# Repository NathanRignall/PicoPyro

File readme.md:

# Pico Pyro v1.0.1
DMX controlled dual pyrotechnic channels.

## Hardware Overview

 - Status LED - (WHITE, GREEN, RED, BLUE, PURPLE)
 - Continuity LED - (GREEN)
 - Fire LED - (RED)
 - Configuration Button
 - Arming Cover
 - DMX In/Out

 - Power+ (3v-50v)
 - Power-
 - Pyro 0/1-
 - Pyro 0/1+

## Modes
The Pico Pyro can be in one of three modes, these are indicated by the status LED.

By default the system enters **active** mode when turned on.

To enter **setup** mode the configuration button must be pressed while being turned on. Setup mode cannot be entered after booting.

If the system detects an invalid configuration during boot the system will enter **failed** mode. To resolved the system must be turned off and back on into setup mode.

### Active
 - Status LED is solid **GREEN** when DMX is detected, **RED** when no DMX signal is detected.
 - Continuity LEDs are **GREEN** when the voltage threshold is met across the pyrotechnic channels. These are used to show if there is a good connection across the hardware connected.
 - Fire LEDs are **RED** when the specified pyrotechnic channel is fired. This occurs when the DMX authorization and fire values are met for that channel.

### Setup
 - Status LED **BLUE**.
 - Continuity LEDs are **GREEN** when the voltage threshold is met across the pyrotechnic channels. These are used to show if there is a good connection across the hardware connected.
 - Fire LEDs and hence pyrotechnic channels off and ***cannot activate***.

### Failed
 - Status LED **PURPLE**.
 - Continuity LEDs off and cannot activate.
 - Fire LEDs and hence pyrotechnic channels off and ***cannot activate***.

## DMX Table

| Channel | Description                         |
| ------- | ----------------------------------- |
| 1       | Pyrotechnic Channel 0 Authorization |
| 2       | Pyrotechnic Channel 1 Authorization |
| 3       | Pyrotechnic Channel 0 Fire          |
| 4       | Pyrotechnic Channel 1 Fire          |

The DMX values to activate the different channels are specified in the configuration tool.

## Setup
Once entering setup mode the system can be configured using the built-in website. This is accessed by connecting to the WiFi network that is broadcast and navigating to the IP address in the chosen browser.

**SSID** - PicoPyro  
**Password** - itsathing  
**URL** - http://10.66.0.1

The user should be presented with the following...

 - Voltage threshold - (0-1023) - Value used to activate the continuity LEDs. This value is dependant on the supplied voltage. When supplied with around 12v an advised threshold value is 100.
 - DMX Address - (1-251) - Base address for all DMX channels.
 - DMX Pyro0 Auth - (0-255) - Value required to activate channel
 - DMX Pyro1 Auth - (0-255) - Value required to activate channel
 - DMX Pyro0 Fire - (0-255) - Value required to activate channel
 - DMX Pyro1 Fire - (0-255) - Value required to activate channel

## Usage Tips
Ensure all connections are attached.

Arming cover can be removed for rehearsals to test the behaviour of the system without activating pyrotechnic channels.  
When the arming cover is removed the channels are electrically disconnected and cannot fire. The continuity LEDs will temporarily stop working. Fire LEDs will work as expected but won't fire the pyrotechnic channels.  
The recommended method of removing the arming cover is by placing a cable tie through the loop and pulling backwards.

Do not set the activation value to 255, this will increase the chance of accidental activation.  
Instead use a selection of unique, different values.

The easiest way to integrate this system into lighting software is by patching 4 dimmer channels.

## Electronics
Voltage dividers are used for the continuity detection.  
Low voltage dropout is in the voltage regulator.

## Troubleshooting
 - The status LED should be constant **GREEN** when in normal operation.
   - Flickering to **RED** DMX connection is unstable
   - Flickering off supplied voltage is too low (especially during firing)
 - When not activating as expected this could be because the Grand Master is lowering the values slightly.
   - To combat this happening set the 'cue' to ignore the Grand Master

## Legal
We accept no responsibility for the consequences of activating a pyrotechnic.

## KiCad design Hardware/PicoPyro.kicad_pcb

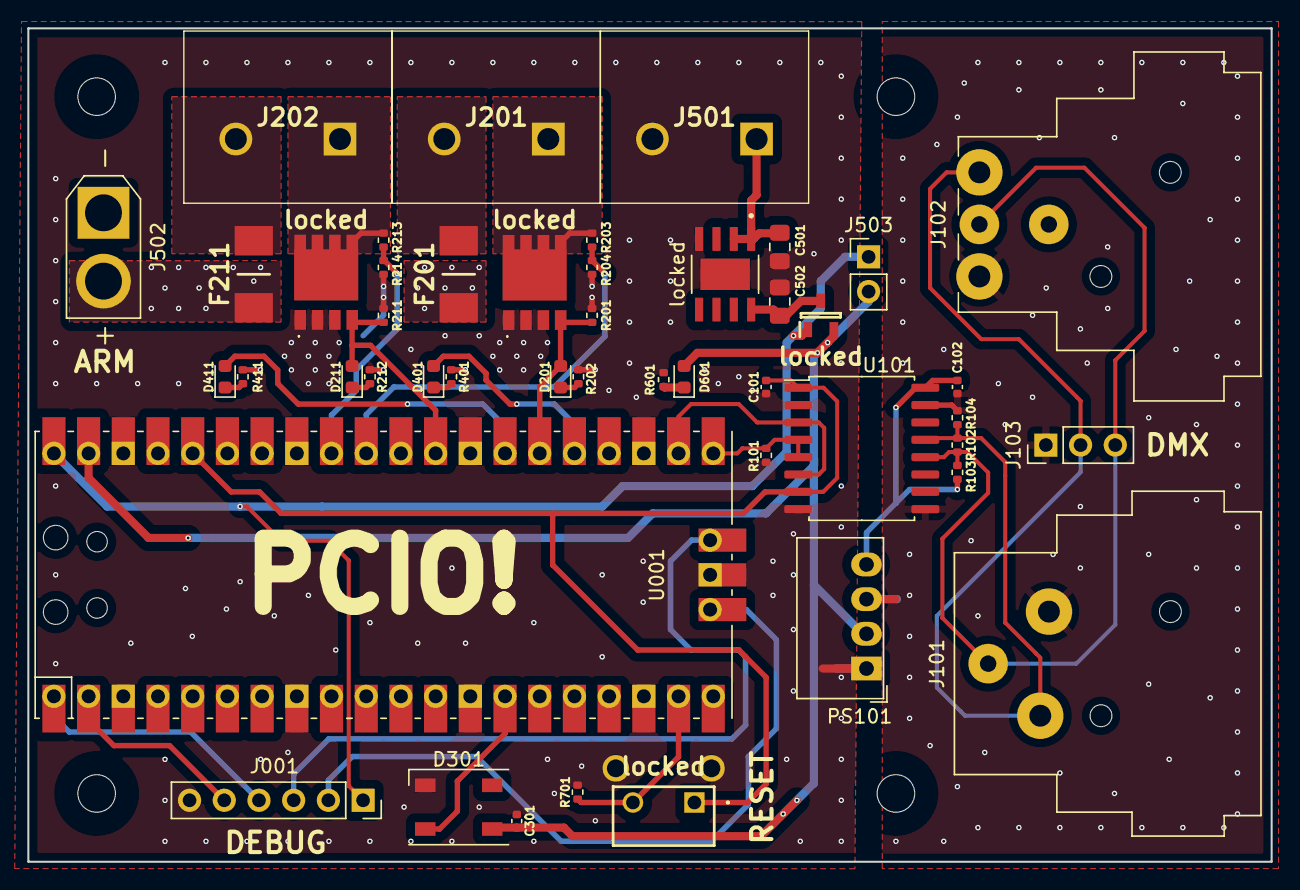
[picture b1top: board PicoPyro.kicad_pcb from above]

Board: 2 copper layers, 91.0 x 61.0 mm, 46 parts (0 on the bottom side), 34 nets.

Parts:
C101, C102, C301: 100n; C_0402_1005Metric
C501, C502: 10u; C_0805_2012Metric_Pad1.18x1.45mm_HandSolder
D201, D211, D401, D411, D601: LED; LED_0603_1608Metric
D301: WS2812B; LED_WS2812B_PLCC4_5.0x5.0mm_P3.2mm
F201, F211: 0679H9100-05; FUSC6125X279N
J001: Conn_01x06; PinSocket_1x06_P2.54mm_Vertical
J101: XLR3; Jack_XLR_Neutrik_NC3FAAH_Horizontal
J102: XLR3; Jack_XLR_Neutrik_NC3MAAH_Horizontal
J103: Conn_01x03; PinHeader_1x03_P2.54mm_Vertical
J201, J202, J501: TB005-762-02BE; TB00576202BE
J502: Conn_01x02; AMASS_XT30U-F_1x02_P5.0mm_Vertical
J503: Conn_01x02; PinHeader_1x02_P2.54mm_Vertical
PS101: MEE1S0503SC; Converter_DCDC_Murata_MEE1SxxxxSC_THT
R101: 2k; R_0402_1005Metric
R102: 120; R_0402_1005Metric
R103, R104: 680; R_0402_1005Metric
R201, R204, R211, R214, R701: 10k; R_0402_1005Metric
R202, R212, R401, R411: 500; R_0402_1005Metric
R203, R213: 150k; R_0402_1005Metric
R601: 1k; R_0402_1005Metric
U001: Pico; RPi_Pico_SMD_TH
U101: ADM2483xRW; SOIC-16W_7.5x10.3mm_P1.27mm
locked: TS11-674-43-BK-100-RA-D; TS1167443BK100RAD
locked#2: TQL850CSV50; SOIC127P600X170-9N
locked#3: DMP2120U-7; SOT96P240X110-3N
locked#4, locked#5: TPH9R506PL,LQ; TPCA8128L1Q

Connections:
+3V3: C101.1, U001.36 (3V3), U101.1 (VDD1), U101.7 (PV), locked.1 (COM)
+5V: C301.1, D301.1 (VDD), D601.2 (A), J503.2, PS101.2 (+Vin), U001.39 (VSYS), locked#3.2
/5V_DMX: C102.1, PS101.4 (+Vout), R103.1, U101.16 (VDD2)
/ARM: F201.2, F211.2, J502.2
/BUTTON_MODE: R701.2, U001.19 (GPIO14), locked.2 (NO)
/DEBUG_CLK: J001.2, U001.41 (SWCLK)
/DEBUG_DIO: J001.3, U001.43 (SWDIO)
/DMX_IO: U001.22 (GPIO17), U101.3 (RxD), U101.6 (TxD)
/DMX_RDM: R101.1, U001.21 (GPIO16), U101.4 (~RE), U101.5 (DE)
/GND_DMX: C102.2, J101.1, J102.1, J103.1, PS101.3 (-Vout), R104.2, U101.9 (GND2), U101.15 (GND2)
/LED_STATUS: D301.4 (DIN), U001.14 (GPIO10)
/PYRO0_FIRE: D201.2 (A), R201.2, U001.26 (GPIO20), locked#4.4 (G)
/PYRO0_LED: D401.2 (A), U001.25 (GPIO19)
/PYRO0_MEASURE: R203.2, R204.2, U001.31 (GPIO26_ADC0)
/PYRO1_FIRE: D211.2 (A), R211.2, U001.29 (GPIO22), locked#5.4 (G)
/PYRO1_LED: D411.2 (A), U001.27 (GPIO21)
/PYRO1_MEASURE: R213.2, R214.2, U001.32 (GPIO27_ADC1)
/UART0_RX: J001.5, U001.2 (GPIO1)
/UART0_TX: J001.4, U001.1 (GPIO0)
GND: C101.2, C301.2, C501.1, C502.2, D301.3 (VSS), J001.6, J501.2, PS101.1 (-Vin), R101.2, R201.1, R202.2, R204.1, R211.1, R212.2, R214.1, R401.2, R411.2, R601.2, R701.1, U001.3 (GND), U001.8 (GND), U001.13 (GND), U001.18 (GND), U001.23 (GND), U001.28 (GND), U001.33 (AGND), U001.38 (GND), U001.42 (GND), U101.2 (GND1), U101.8 (GND1), locked.3 (GND_1), locked.4 (GND_2), locked#2.4 (GND), locked#2.9 (EXP), locked#4.1 (S_1), locked#4.2 (S_2), locked#4.3 (S_3), locked#5.1 (S_1), locked#5.2 (S_2), locked#5.3 (S_3)
unnamed: C501.2, J501.1, J502.1, locked#2.1 (IN), locked#2.2 (EN)
unnamed: D201.1 (K), R202.1
unnamed: D211.1 (K), R212.1
unnamed: D401.1 (K), R401.1
unnamed: D411.1 (K), R411.1
unnamed: D601.1 (K), R601.1
unnamed: J101.2, J102.2, J103.2, R102.2, R104.1, U101.13 (B)
unnamed: J101.3, J102.3, J103.3, R102.1, R103.2, U101.12 (A)
unnamed: J201.1, R203.1, locked#4.5 (D_1), locked#4.6 (D_2), locked#4.7 (D_3), locked#4.8 (D_4), locked#4.9 (D_5)
unnamed: F201.1, J201.2
unnamed: J202.1, R213.1, locked#5.5 (D_1), locked#5.6 (D_2), locked#5.7 (D_3), locked#5.8 (D_4), locked#5.9 (D_5)
unnamed: F211.1, J202.2
unnamed: C502.1, locked#2.8 (OUT), locked#3.3
VBUS: J001.1, J503.1, U001.40 (VBUS), locked#3.1

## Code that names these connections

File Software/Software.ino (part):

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
const int reset_button_pin = 14;

const int pyro0_measure_pin = 26;
const int pyro1_measure_pin = 27;

// ------ Output sepecific variables ------

const int led_pin = 25;

const int pyro0_led_pin = 19;
const int pyro1_led_pin = 21;

const int status_led_pin = 10;
int status_led_format = NEO_GRB + NEO_KHZ800;
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
// ------ Pyro sepecific variables ------

const int pyro0_fire_pin = 20;
const int pyro1_fire_pin = 22;

// ------ DMX specific variables ------

const int dmx_rdm_pin = 16;
const int dmx_io_pin = 17;

const int dmx_start_channel = 1;
const int dmx_num_channels = 255;
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  digitalWrite(led_pin, 0);
  Serial.println("Inbuilt led setup \n");

  pinMode(pyro0_led_pin, OUTPUT);
  digitalWrite(pyro0_led_pin, 0);
  Serial.println("Pyro0 led setup \n");

  pinMode(pyro1_led_pin, OUTPUT);
  digitalWrite(pyro1_led_pin, 0);
  Serial.println("Pyro1 led setup \n");

  // setup the status led and set it to white
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    return;
  }

  pinMode(pyro0_fire_pin, OUTPUT);
  digitalWrite(pyro0_fire_pin, 0);
  Serial.println("Pyro0 fire setup \n");

  pinMode(pyro1_fire_pin, OUTPUT);
  digitalWrite(pyro1_fire_pin, 0);
  Serial.println("Pyro1 fire setup \n");

  // Set done to true
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  }

  // Setup RDM
  pinMode(pyro1_fire_pin, OUTPUT);
  digitalWrite(pyro1_fire_pin, 0);
  Serial.println("DMX RDM setup \n");

  // Setup DMX
  dmxInput.begin(dmx_io_pin, dmx_start_channel, dmx_num_channels);
  dmxInput.read_async(dmx_buffer);
  Serial.println("DMX input started \n");

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
void loop_inputs(Inputs *inputs)
{
  inputs->pyro0_measure = analogRead(pyro0_measure_pin);
  inputs->pyro1_measure = analogRead(pyro1_measure_pin);
}

void loop_outputs(Outputs outputs)
{
  digitalWrite(pyro0_led_pin, outputs.pyro0_led);
  digitalWrite(pyro1_led_pin, outputs.pyro1_led);

  status_led_pixels->clear();

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
void loop_pyro(Pyro pyro)
{
  digitalWrite(pyro0_fire_pin, pyro.pyro0_fire);
  digitalWrite(pyro1_fire_pin, pyro.pyro1_fire);
}

void loop_dmx(DMX *dmx)
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
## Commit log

2022-11-06 Software updates
2022-11-06 Separate code into files
2022-11-13 Remove next app
2022-11-19 Add copyright notices
2022-11-19 Close file in correct place
2022-11-19 Add software version notice
2022-11-19 Add version message to html
2022-11-19 Fix slow dmx arrival
2022-11-20 Documentation manual added
2022-11-20 Add title to documentation
2022-11-20 Spell corrections
2022-11-20 Add method to remove cover
2022-11-20 Colours in bold
2022-11-21 Add more to docs

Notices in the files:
Software/Software.ino:
Copyright (C) 2022 Nathan Rignall
